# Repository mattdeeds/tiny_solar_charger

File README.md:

# Tiny Solar Charger
Less than one inch square solar charging board based on the bq25504 solar harvesting ic with onboard solar cell for low power applications

## Parts 
- KXOB25-04X3F-TR: MONOCRYSTL SOLAR CELL 22MW 2.07V 
- TI BQ25504: Ultra Low-Power Boost Converter With Battery Management 
### Configuration
Currently configured for single cell li-ion batteries but I've tested it with supercapacitors with voltage ratings over 4.2v

BAT_OV = 4.2v
BAT_UV = 3.0v 

Configuration resistor values: 
- R6 = 4.02M
- R7 = 16M 
- R8 = 4.42M
- R9 = 5.49M
- R10 = 4.22M
- R11 = 5.9M
- R12 = 5.620M
- R13 = 3.830M 
- R14 = 0.619M

### Board Pinout and Overview

### Todo/improvements
- Schematic specifies an inductor that I'm not actually using, switched to a higher max current 
- Currently using inductor with 300ma max current, datasheet specifies >300ma

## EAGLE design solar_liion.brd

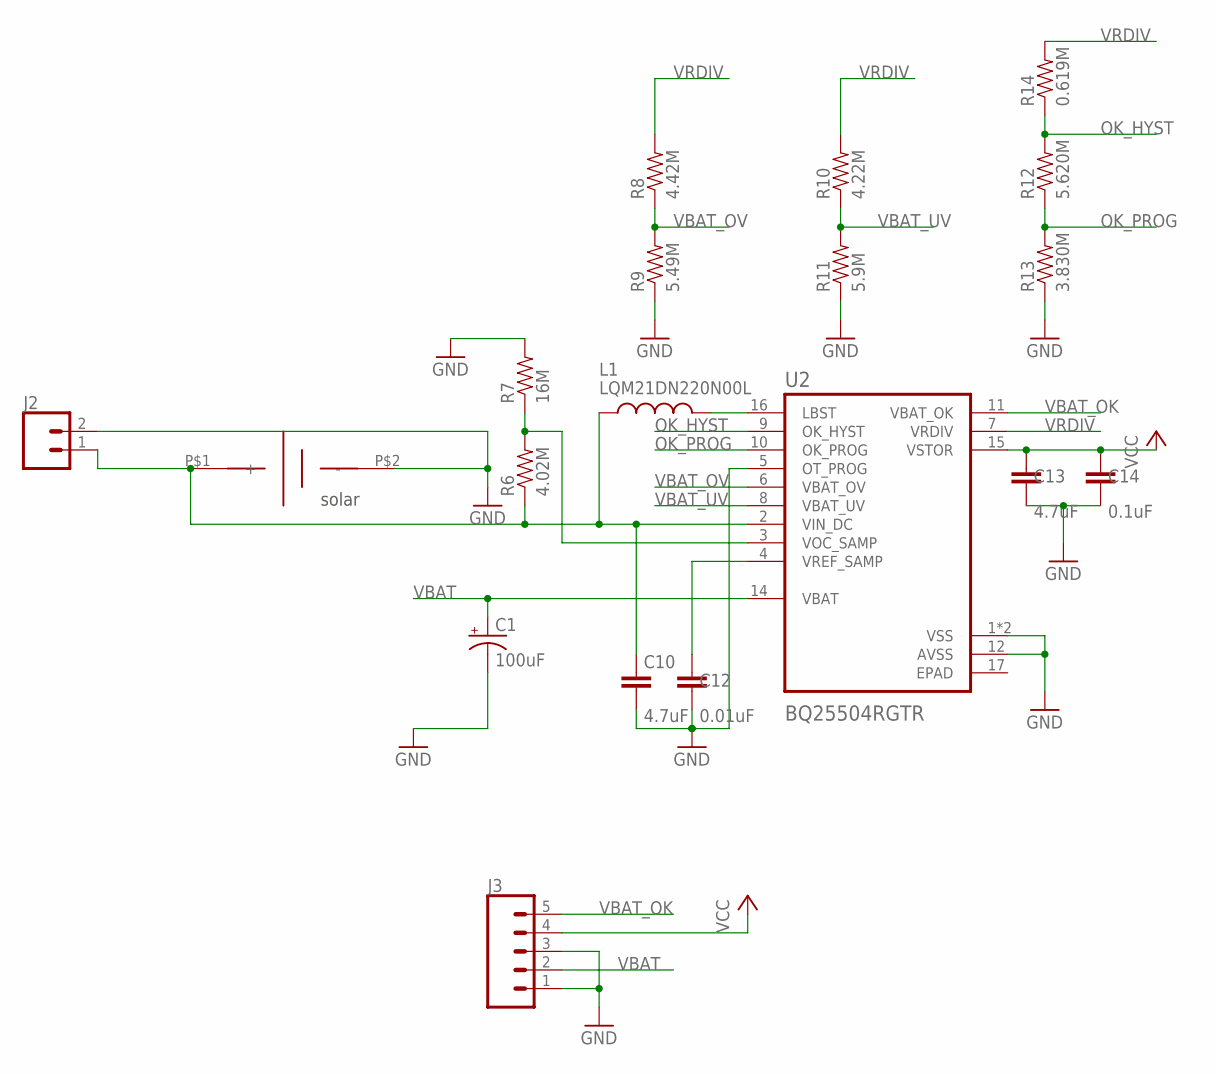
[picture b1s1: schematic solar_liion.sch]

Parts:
C1: 100uF; EIA7343
C10, C13: 4.7uF; 0603
C12: 0.01uF; 0603
C14: 0.1uF; 0603
J2: CONN_02; 1X02
J3: CONN_05; 1X05
L1: LQM21DN220N00L; INDC2012X145N
R6: 4.02M; 0603
R7: 16M; 0603
R8: 4.42M; 0603
R9: 5.49M; 0603
R10: 4.22M; 0603
R11: 5.9M; 0603
R12: 5.620M; 0603
R13: 3.830M; 0603
R14: 0.619M; 0603
U2: BQ25504RGTR; QFN50P300X300X100-17N
U$3: KXOB25-04X3F-TR

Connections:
EPAD: U2.17 (EPAD)
GND: C1.C (-), C10.2, C12.2, C13.2, C14.2, J2.2, J3.1, J3.3, R7.2, R9.1, R11.1, R13.1, U2.1 (VSS), U2.5 (OT_PROG), U2.12 (AVSS), U2.13 (VSS), U$3.P$2 (-)
unnamed: C10.1, J2.1, L1.1, R6.1, U2.2 (VIN_DC), U$3.P$1 (+)
unnamed: L1.2, U2.16 (LBST)
unnamed: C12.1, U2.4 (VREF_SAMP)
unnamed: R6.2, R7.1, U2.3 (VOC_SAMP)
OK_HYST: R12.2, R14.1, U2.9 (OK_HYST)
OK_PROG: R12.1, R13.2, U2.10 (OK_PROG)
VBAT: C1.A (+), J3.2, U2.14 (VBAT)
VBAT_OK: J3.5, U2.11 (VBAT_OK)
VBAT_OV: R8.1, R9.2, U2.6 (VBAT_OV)
VBAT_UV: R10.1, R11.2, U2.8 (VBAT_UV)
VCC: C13.1, C14.1, J3.4, U2.15 (VSTOR)
VRDIV: R8.2, R10.2, R14.2, U2.7 (VRDIV)

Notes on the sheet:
solar

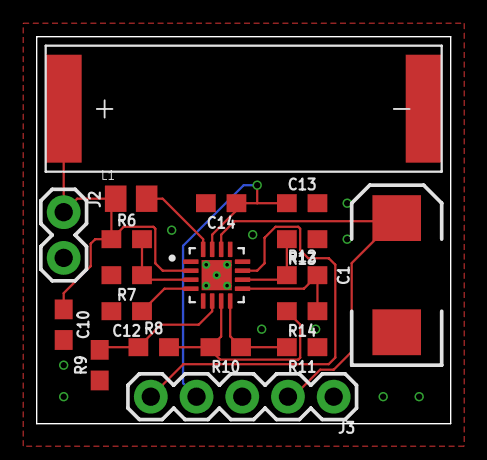
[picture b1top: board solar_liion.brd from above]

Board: 2 copper layers, 23.0 x 21.5 mm, 19 parts (0 on the bottom side), 13 nets.

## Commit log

2021-03-25 add board files

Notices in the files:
parts and their libraries:
SparkFun-Capacitors: Licensing: Creative Commons ShareAlike 4.0 International - https://creativecommons.org/licenses/by-sa/4.0
